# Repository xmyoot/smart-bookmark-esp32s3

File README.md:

# Smart Bookmark ESP32-S3 BLE

### Ultra-Low-Power Voice Recording & Audio Annotation Bookmark

---

## 3D Hardware Overview

---

## Project Highlights
The **Smart Bookmark** is a commercial-grade, ultra-thin 4-layer hardware device designed to fit cleanly inside a book or notebook. It records spoken voice memos, audio book notes, and timestamps via a single push-button, storing high-quality audio onto 16 MB onboard flash and syncing via Bluetooth Low Energy (BLE 5.0) to an accompanying mobile application.

### Key Features
- **Processor:** Espressif **ESP32-S3-WROOM-1** (Dual-core Xtensa LX7 @ 240 MHz, 2.4 GHz Wi-Fi & BLE 5.0).
- **Audio Capture:** Knowles digital PDM / MEMS microphone (`MK1`) with hardware audio filtering.
- **Local Storage:** 16 MB high-speed SPI NOR Flash (`U6`) dedicated for raw and compressed audio memo storage.
- **Power Management:**
  - Integrated single-cell LiPo charger (`U3`, TP4056/MCP73831 class) with USB-C power input (`J1`).
  - Ultra-low quiescent current 3.3V LDO regulator (`U5`).
  - Precision battery level monitoring voltage divider (`BATT SENSE` / `U4`).
- **Physical Design:**
  - 37.1 × 52.1 mm form factor with rounded corners to protect paper pages.
  - Symmetrical component placement with clear silkscreen identifiers (`STATUS LED`, `16MB FLASH`, `RECORD SW1`, `U3 CHARGER`, `3V3 REG`).
  - Dedicated bottom-side battery cradle target (`CELL 25 × 30 mm`) and 2×3 pogo-pin programming test matrix (`GND`, `3V3`, `EN`, `BOOT`, `TX`, `RX`).

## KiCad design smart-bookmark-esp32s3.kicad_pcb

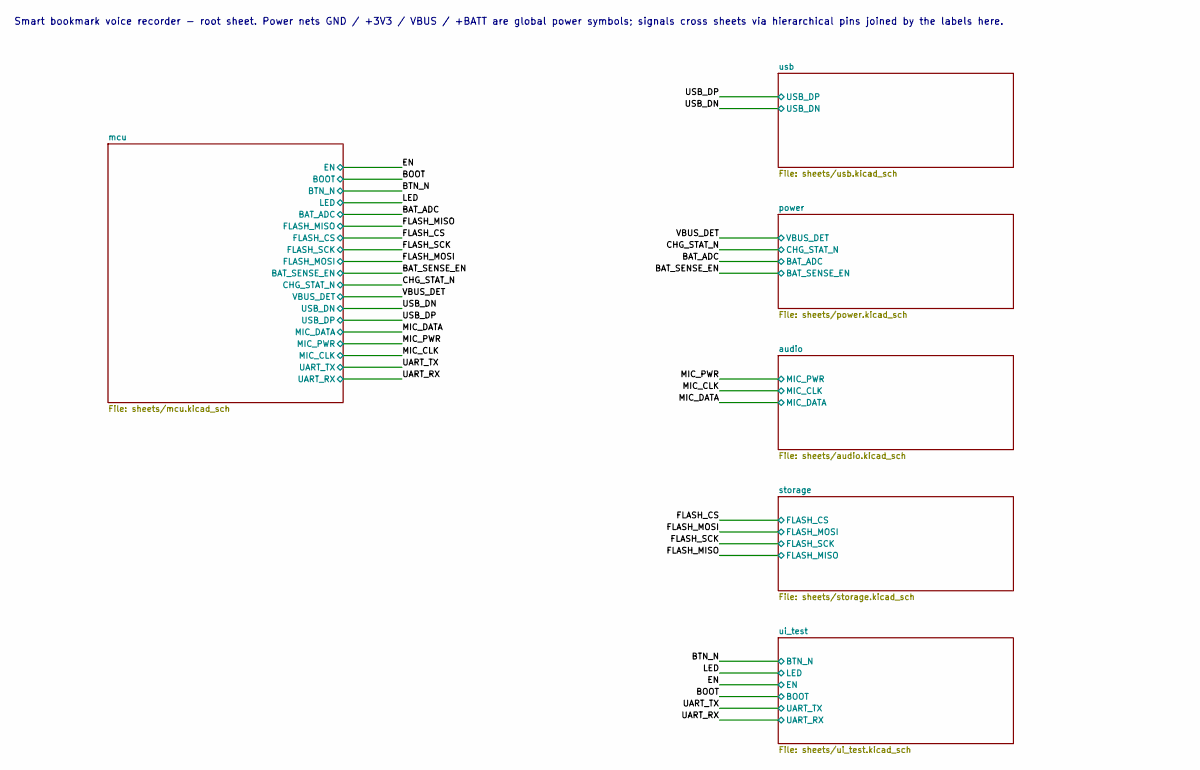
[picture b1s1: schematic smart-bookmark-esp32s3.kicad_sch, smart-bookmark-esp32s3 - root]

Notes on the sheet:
Smart bookmark voice recorder - root sheet. Power nets GND / +3V3 / VBUS / +BATT are global power symbols; signals cross sheets via hierarchical pins joined by the labels here.

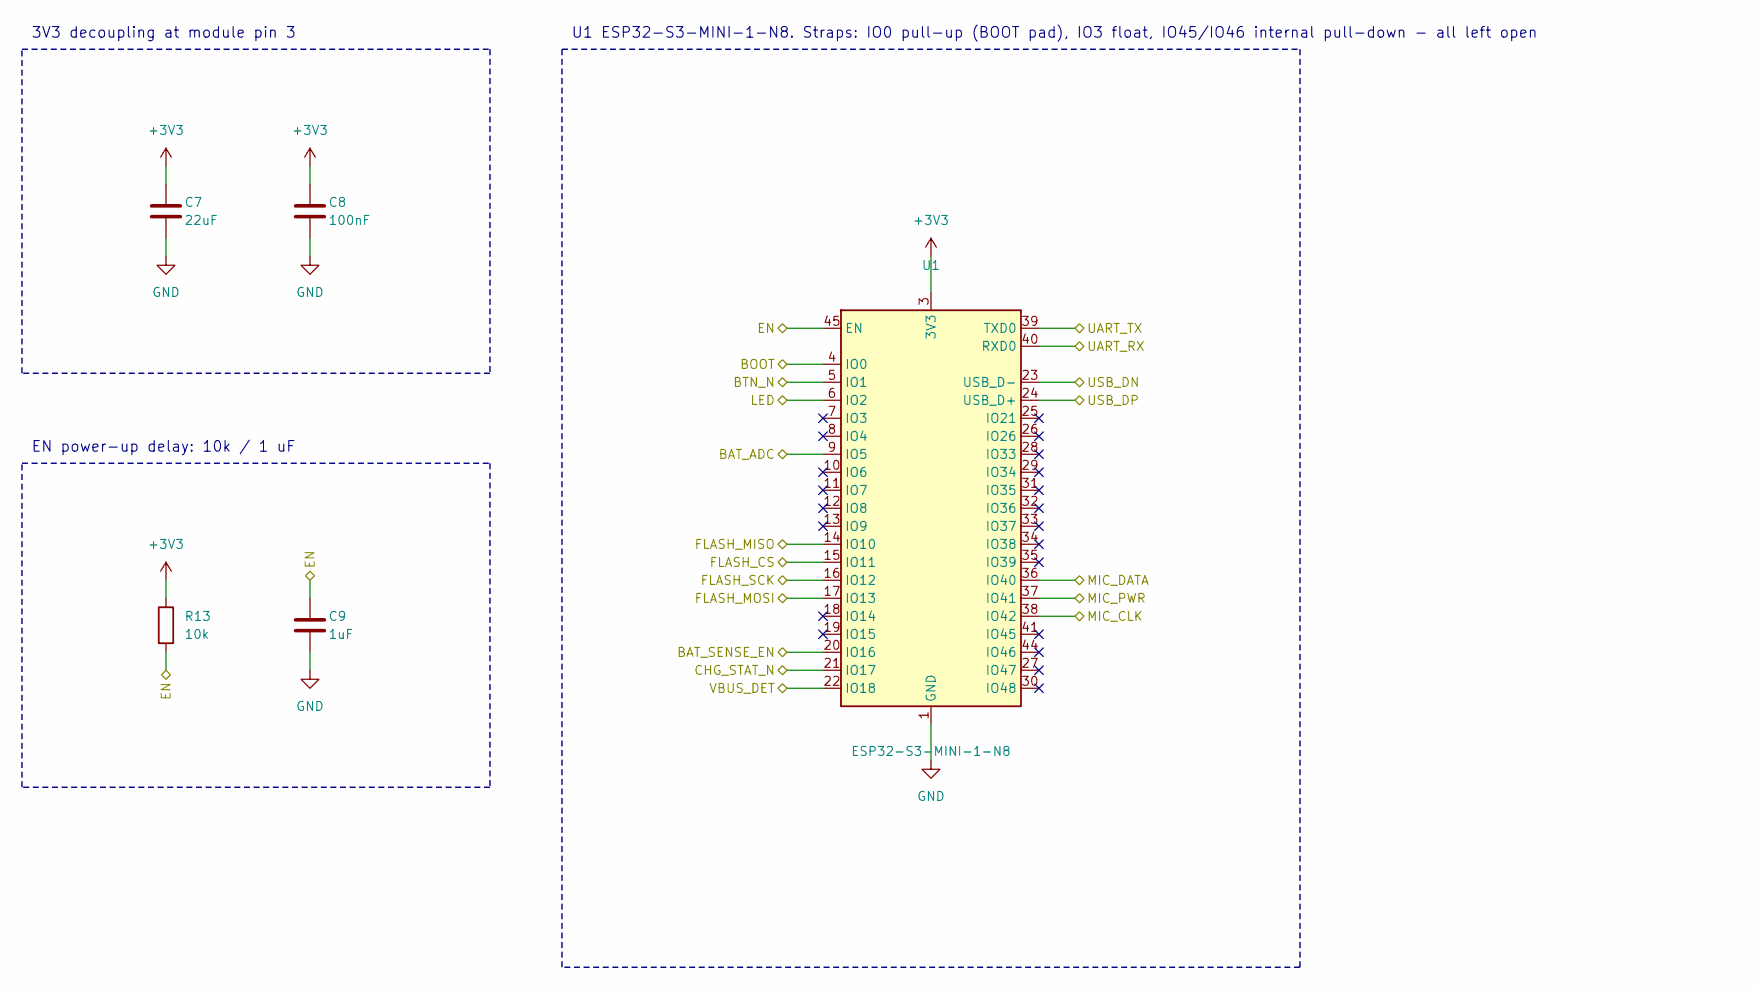
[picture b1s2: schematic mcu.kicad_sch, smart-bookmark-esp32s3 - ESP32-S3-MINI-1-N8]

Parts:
C7: 22uF; C_0805_2012Metric; MPN CL21A226MAQNNNE; LCSC C45783
C8: 100nF; C_0402_1005Metric; MPN CL05B104KO5NNNC; LCSC C1525
C9: 1uF; C_0402_1005Metric; MPN CL05A105KA5NQNC; LCSC C52923
R13: 10k; R_0402_1005Metric; MPN 0402WGF1002TCE; LCSC C25744
U1: ESP32-S3-MINI-1-N8; ESP32-S2-MINI-1; MPN ESP32-S3-MINI-1-N8; LCSC C2913206

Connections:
+3V3: C7.1, C8.1, R13.1, U1.3 (3V3); also elsewhere on the board
/BAT_ADC: U1.9 (IO5); also elsewhere on the board
/BAT_SENSE_EN: U1.20 (IO16); also elsewhere on the board
/BOOT: U1.4 (IO0); also elsewhere on the board
/BTN_N: U1.5 (IO1); also elsewhere on the board
/CHG_STAT_N: U1.21 (IO17); also elsewhere on the board
/EN: C9.1, R13.2, U1.45 (EN); also elsewhere on the board
/FLASH_CS: U1.15 (IO11); also elsewhere on the board
/FLASH_MISO: U1.14 (IO10); also elsewhere on the board
/FLASH_MOSI: U1.17 (IO13); also elsewhere on the board
/FLASH_SCK: U1.16 (IO12); also elsewhere on the board
/LED: U1.6 (IO2); also elsewhere on the board
/MIC_CLK: U1.38 (IO42); also elsewhere on the board
/MIC_DATA: U1.36 (IO40); also elsewhere on the board
/MIC_PWR: U1.37 (IO41); also elsewhere on the board
/UART_RX: U1.40 (RXD0); also elsewhere on the board
/UART_TX: U1.39 (TXD0); also elsewhere on the board
/USB_DN: U1.23 (USB_D-); also elsewhere on the board
/USB_DP: U1.24 (USB_D+); also elsewhere on the board
/VBUS_DET: U1.22 (IO18); also elsewhere on the board
GND: C7.2, C8.2, C9.2, U1.1 (GND), U1.2 (GND), U1.42 (GND), U1.43 (GND), U1.46 (GND), U1.47 (GND), U1.48 (GND), U1.49 (GND), U1.50 (GND), U1.51 (GND), U1.52 (GND), U1.53 (GND), U1.54 (GND), U1.55 (GND), U1.56 (GND), U1.57 (GND), U1.58 (GND), U1.59 (GND), U1.60 (GND), U1.61 (GND), U1.62 (GND), U1.63 (GND), U1.64 (GND), U1.65 (GND); also elsewhere on the board

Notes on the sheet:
U1 ESP32-S3-MINI-1-N8. Straps: IO0 pull-up (BOOT pad), IO3 float, IO45/IO46 internal pull-down - all left open
3V3 decoupling at module pin 3
EN power-up delay: 10k / 1 uF

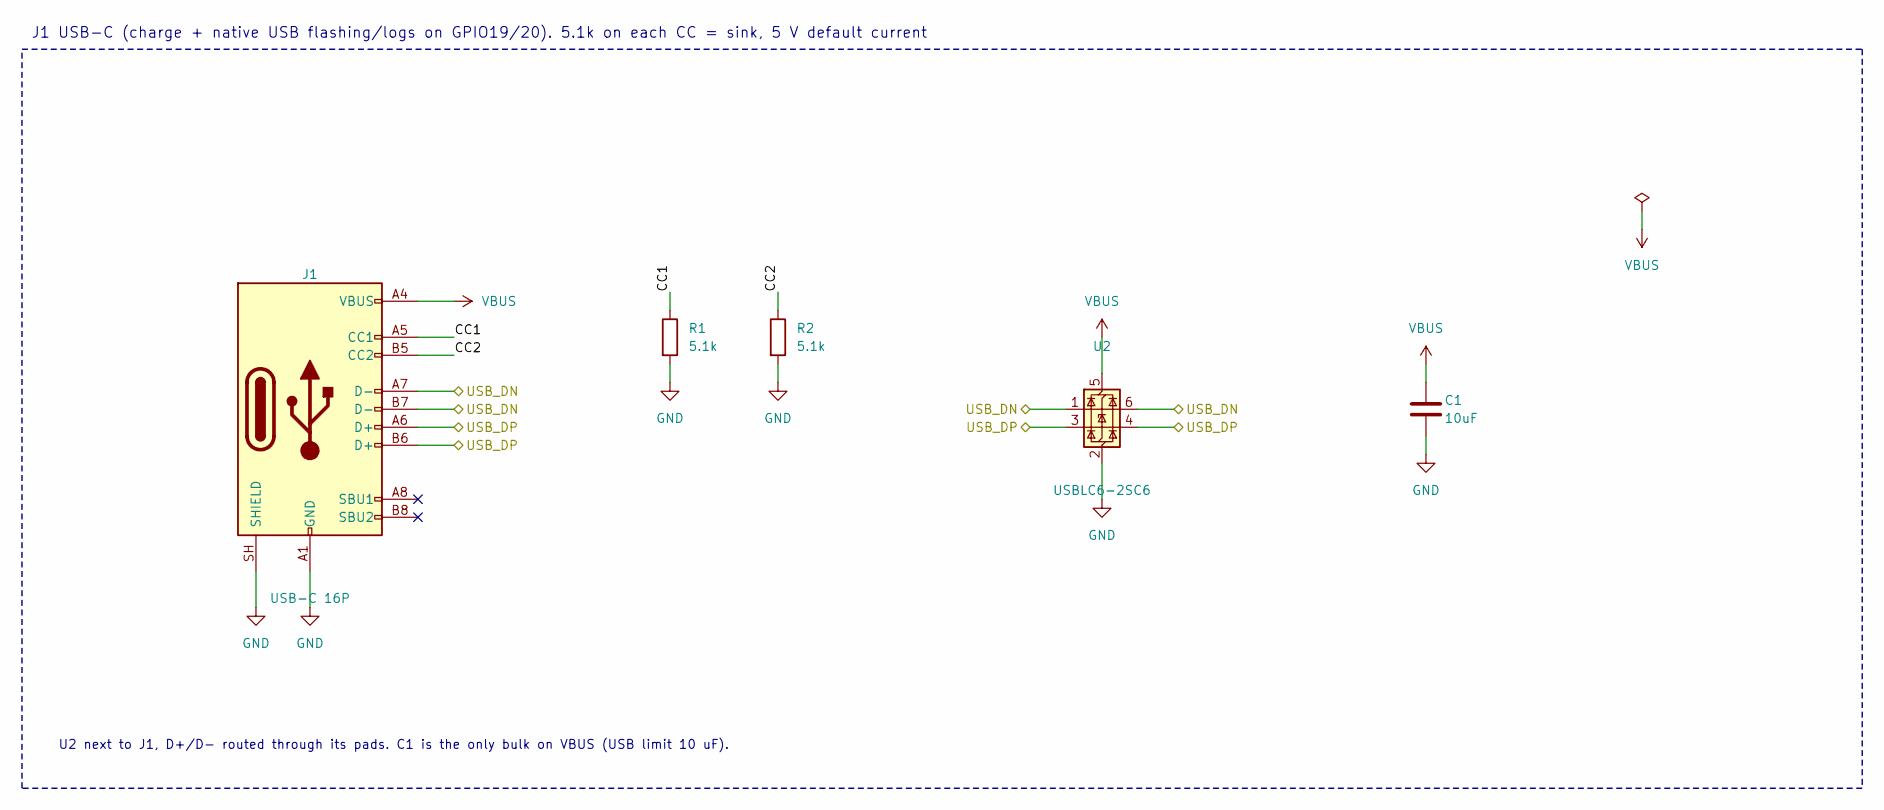
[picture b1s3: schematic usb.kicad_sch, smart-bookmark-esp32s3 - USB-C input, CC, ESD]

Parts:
C1: 10uF; C_0603_1608Metric; MPN CL10A106KP8NNNC; LCSC C19702
J1: USB-C 16P; USB_C_Receptacle_HRO_TYPE-C-31-M-12; MPN TYPE-C-31-M-12; LCSC C165948
R1, R2: 5.1k; R_0402_1005Metric; MPN 0402WGF5101TCE; LCSC C25905
U2: USBLC6-2SC6; SOT-23-6; MPN USBLC6-2SC6; LCSC C7519

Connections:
/USB_DN: J1.A7 (D-), J1.B7 (D-), U2.1 (I/O1), U2.6 (I/O1); also elsewhere on the board
/USB_DP: J1.A6 (D+), J1.B6 (D+), U2.3 (I/O2), U2.4 (I/O2); also elsewhere on the board
/usb/CC1: J1.A5 (CC1), R1.1
/usb/CC2: J1.B5 (CC2), R2.1
GND: C1.2, J1.A1 (GND), J1.A12 (GND), J1.B1 (GND), J1.B12 (GND), J1.SH (SHIELD), R1.2, R2.2, U2.2 (GND); also elsewhere on the board
VBUS: C1.1, J1.A4 (VBUS), J1.A9 (VBUS), J1.B4 (VBUS), J1.B9 (VBUS), U2.5 (VBUS); also elsewhere on the board

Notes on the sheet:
J1 USB-C (charge + native USB flashing/logs on GPIO19/20). 5.1k on each CC = sink, 5 V default current
U2 next to J1, D+/D- routed through its pads. C1 is the only bulk on VBUS (USB limit 10 uF).

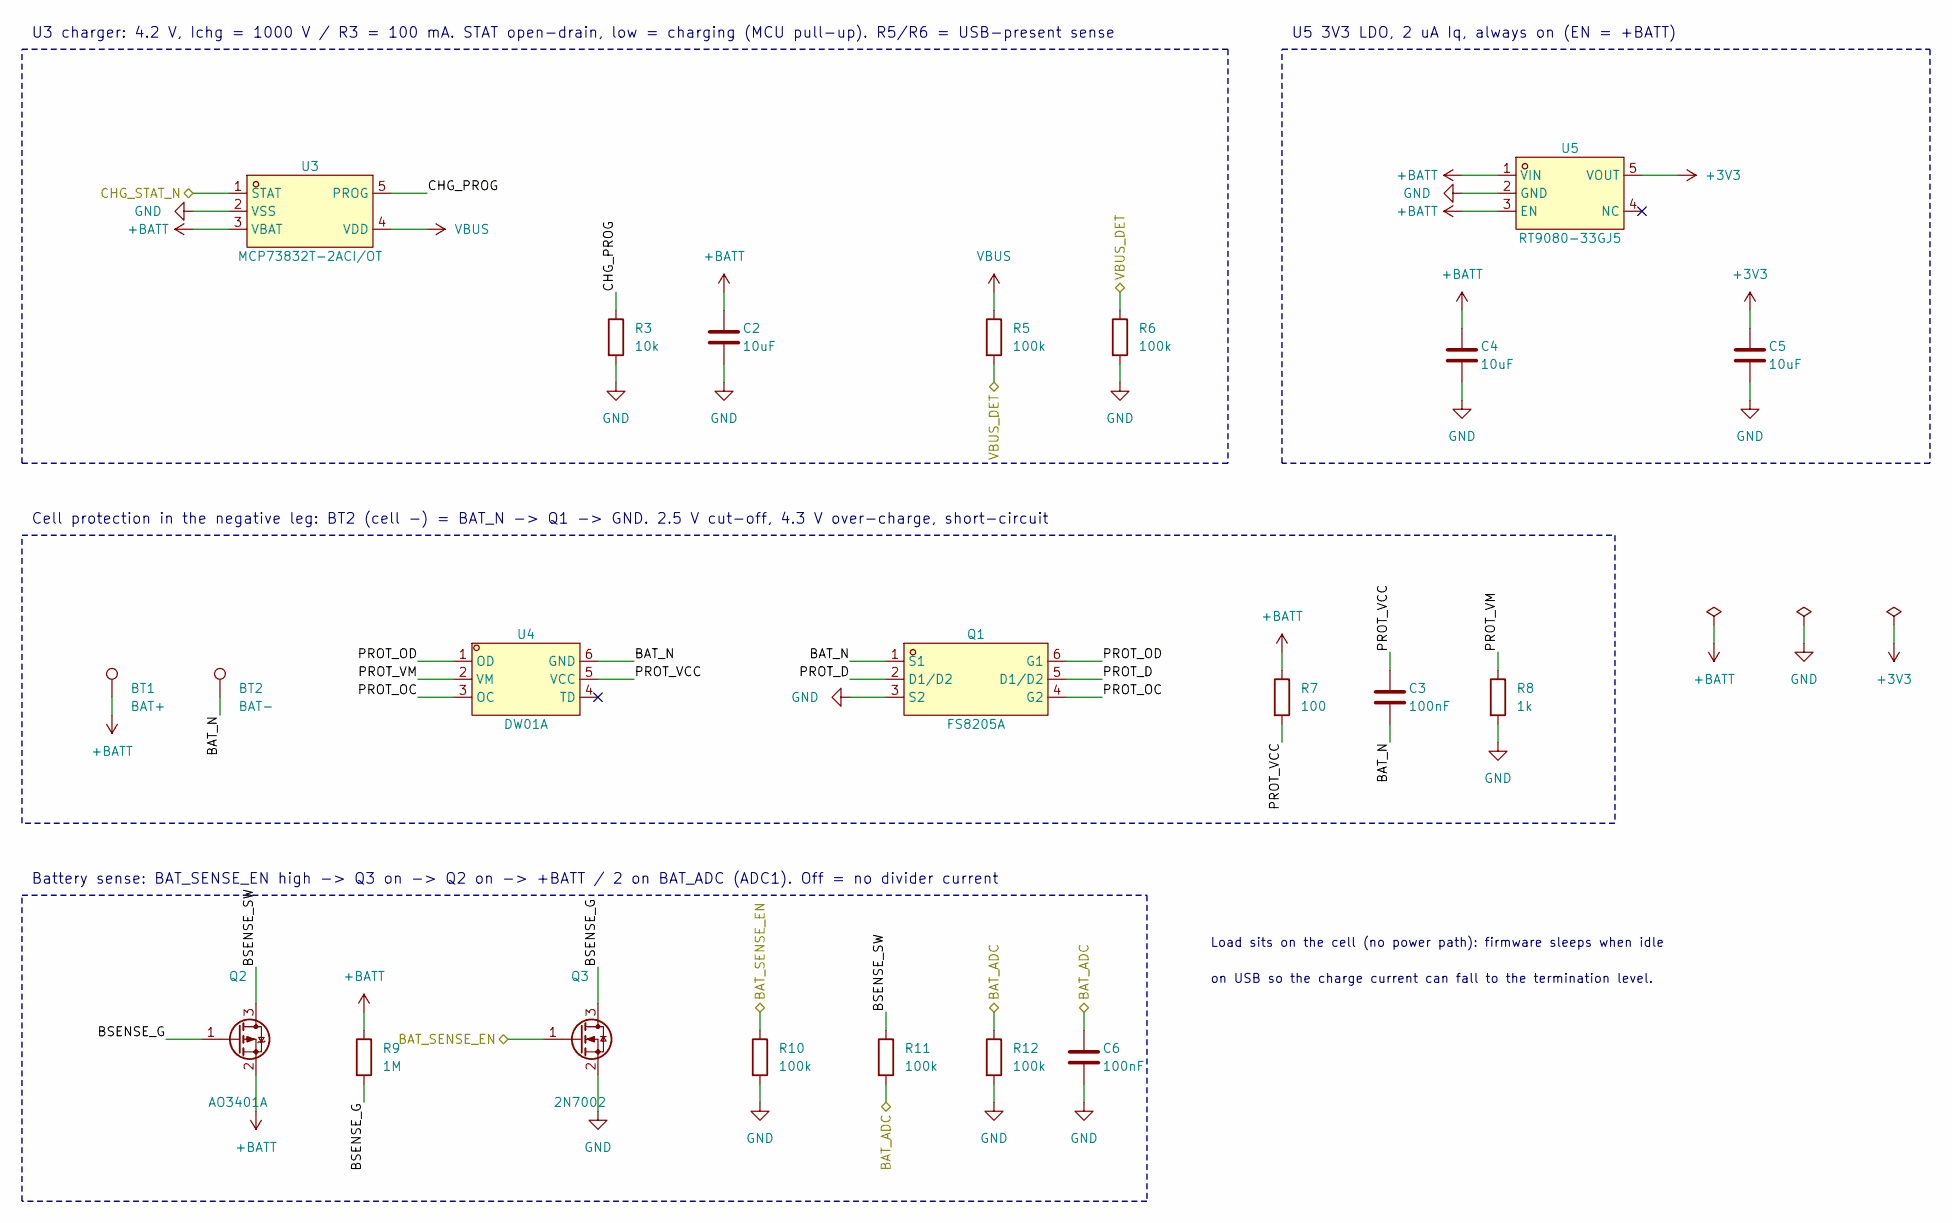
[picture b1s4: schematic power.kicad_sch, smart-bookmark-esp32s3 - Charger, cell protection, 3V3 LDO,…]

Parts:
BT1: BAT+; TestPoint_Pad_2.5x2.5mm
BT2: BAT-; TestPoint_Pad_2.5x2.5mm
C2, C4, C5: 10uF; C_0603_1608Metric; MPN CL10A106KP8NNNC; LCSC C19702
C3, C6: 100nF; C_0402_1005Metric; MPN CL05B104KO5NNNC; LCSC C1525
Q1: FS8205A; SOT-23-6; MPN FS8205A; LCSC C908265
Q2: AO3401A; SOT-23; MPN AO3401A; LCSC C15127
Q3: 2N7002; SOT-23; MPN 2N7002; LCSC C8545
R3: 10k; R_0402_1005Metric; MPN 0402WGF1002TCE; LCSC C25744
R5, R6, R10, R11, R12: 100k; R_0402_1005Metric; MPN 0402WGF1003TCE; LCSC C25741
R7: 100; R_0402_1005Metric; MPN 0402WGF1000TCE; LCSC C25076
R8: 1k; R_0402_1005Metric; MPN 0402WGF1001TCE; LCSC C11702
R9: 1M; R_0402_1005Metric; MPN 0402WGF1004TCE; LCSC C26083
U3: MCP73832T-2ACI/OT; SOT-23-5; MPN MCP73832T-2ACI/OT; LCSC C38066
U4: DW01A; SOT-23-6; MPN DW01A; LCSC C351410
U5: RT9080-33GJ5; TSOT-23-5; MPN RT9080-33GJ5; LCSC C841192

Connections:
+3V3: C5.1, U5.5 (VOUT); also elsewhere on the board
+BATT: BT1.1, C2.1, C4.1, Q2.2 (S), R7.1, R9.1, U3.3 (VBAT), U5.1 (VIN), U5.3 (EN); also elsewhere on the board
/BAT_ADC: C6.1, R11.2, R12.1; also elsewhere on the board
/BAT_SENSE_EN: Q3.1 (G), R10.1; also elsewhere on the board
/CHG_STAT_N: U3.1 (STAT); also elsewhere on the board
/VBUS_DET: R5.2, R6.1; also elsewhere on the board
/power/BAT_N: BT2.1, C3.2, Q1.1 (S1), U4.6 (GND)
/power/BSENSE_G: Q2.1 (G), Q3.3 (D), R9.2
/power/BSENSE_SW: Q2.3 (D), R11.1
/power/CHG_PROG: R3.1, U3.5 (PROG)
/power/PROT_D: Q1.2 (D1/D2), Q1.5 (D1/D2)
/power/PROT_OC: Q1.4 (G2), U4.3 (OC)
/power/PROT_OD: Q1.6 (G1), U4.1 (OD)
/power/PROT_VCC: C3.1, R7.2, U4.5 (VCC)
/power/PROT_VM: R8.1, U4.2 (VM)
GND: C2.2, C4.2, C5.2, C6.2, Q1.3 (S2), Q3.2 (S), R3.2, R6.2, R8.2, R10.2, R12.2, U3.2 (VSS), U5.2 (GND); also elsewhere on the board
VBUS: R5.1, U3.4 (VDD); also elsewhere on the board

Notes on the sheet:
U3 charger: 4.2 V, Ichg = 1000 V / R3 = 100 mA. STAT open-drain, low = charging (MCU pull-up). R5/R6 = USB-present sense
U5 3V3 LDO, 2 uA Iq, always on (EN = +BATT)
Cell protection in the negative leg: BT2 (cell -) = BAT_N -> Q1 -> GND. 2.5 V cut-off, 4.3 V over-charge, short-circuit
Battery sense: BAT_SENSE_EN high -> Q3 on -> Q2 on -> +BATT / 2 on BAT_ADC (ADC1). Off = no divider current
Load sits on the cell (no power path): firmware sleeps when idle
on USB so the charge current can fall to the termination level.

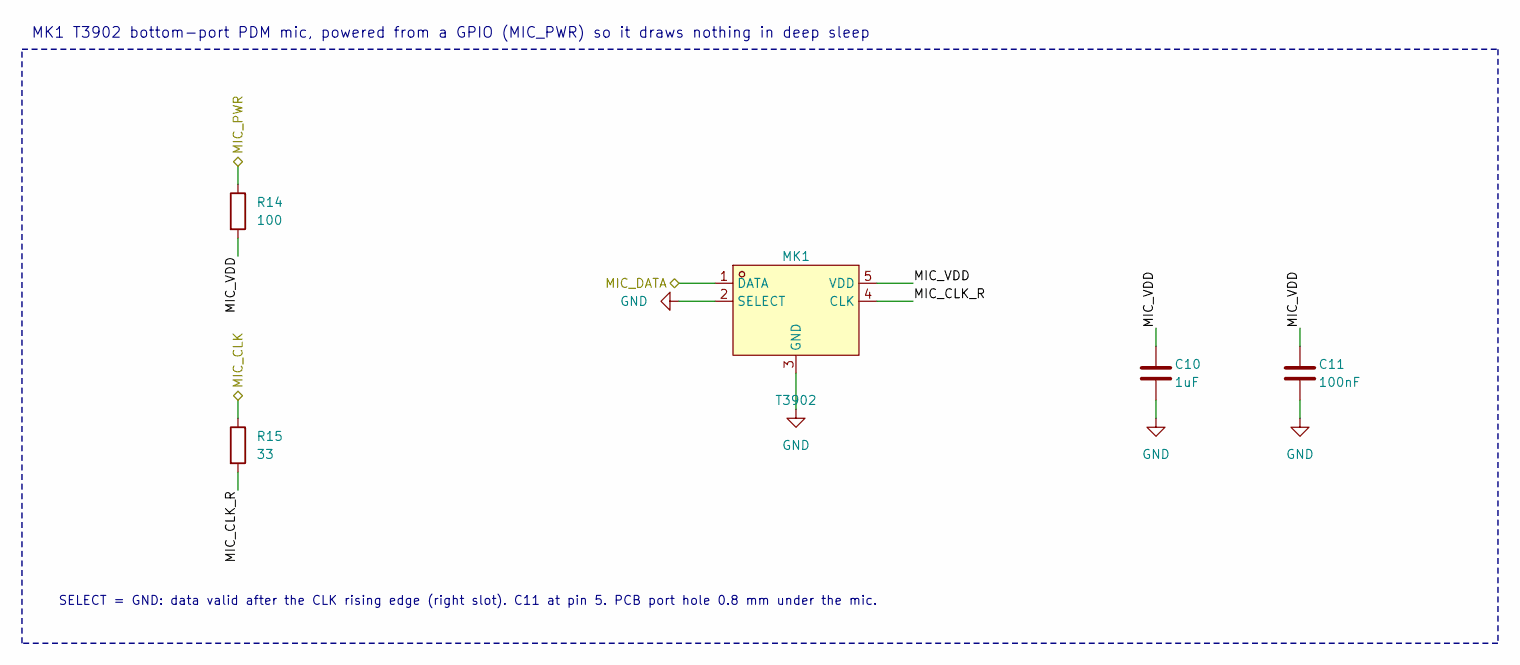
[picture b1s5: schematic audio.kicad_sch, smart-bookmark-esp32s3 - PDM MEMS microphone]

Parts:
C10: 1uF; C_0402_1005Metric; MPN CL05A105KA5NQNC; LCSC C52923
C11: 100nF; C_0402_1005Metric; MPN CL05B104KO5NNNC; LCSC C1525
MK1: T3902; MIC-SMD_5P-L3.5-W2.7-TL_MMICT390200012; MPN MMICT390200012; LCSC C3171752
R14: 100; R_0402_1005Metric; MPN 0402WGF1000TCE; LCSC C25076
R15: 33; R_0402_1005Metric; MPN 0402WGF330JTCE; LCSC C25105

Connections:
/MIC_CLK: R15.1; also elsewhere on the board
/MIC_DATA: MK1.1 (DATA); also elsewhere on the board
/MIC_PWR: R14.1; also elsewhere on the board
/audio/MIC_CLK_R: MK1.4 (CLK), R15.2
/audio/MIC_VDD: C10.1, C11.1, MK1.5 (VDD), R14.2
GND: C10.2, C11.2, MK1.2 (SELECT), MK1.3 (GND); also elsewhere on the board

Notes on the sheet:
MK1 T3902 bottom-port PDM mic, powered from a GPIO (MIC_PWR) so it draws nothing in deep sleep
SELECT = GND: data valid after the CLK rising edge (right slot). C11 at pin 5. PCB port hole 0.8 mm under the mic.

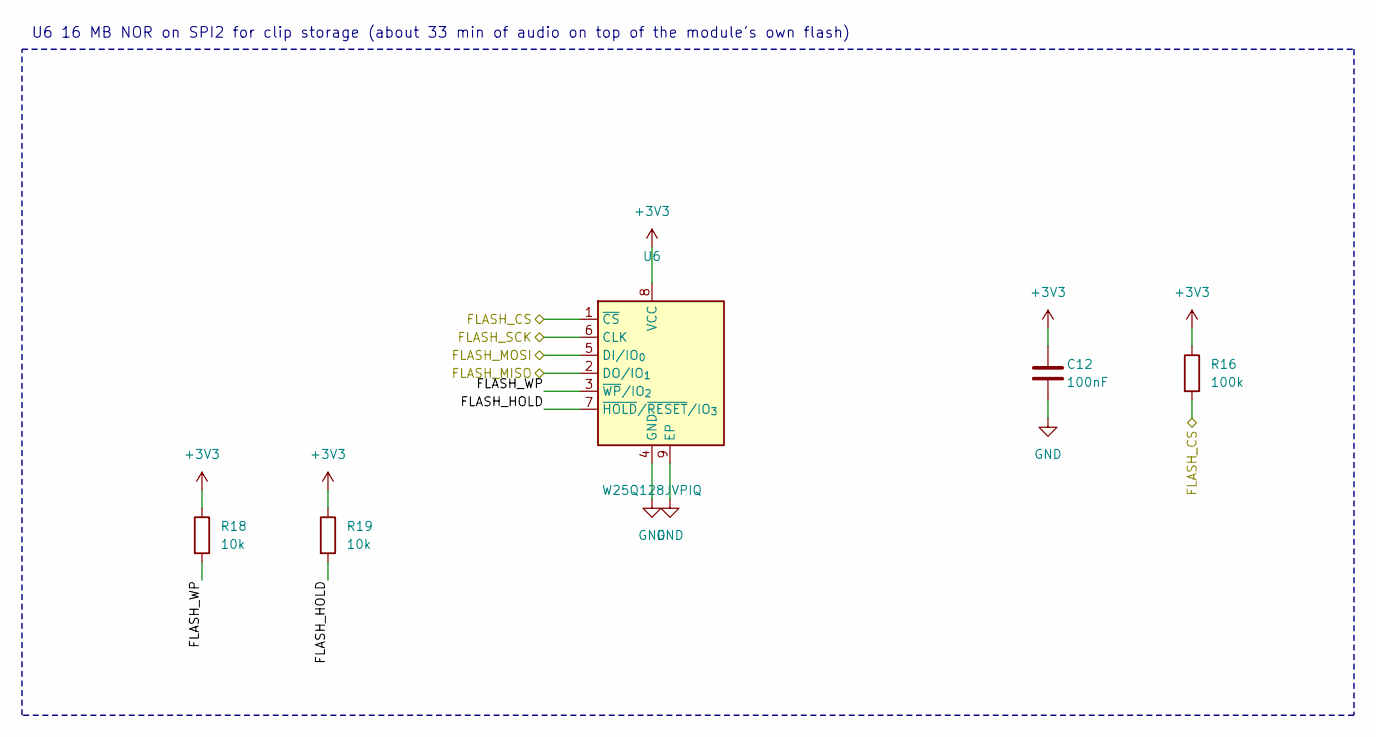
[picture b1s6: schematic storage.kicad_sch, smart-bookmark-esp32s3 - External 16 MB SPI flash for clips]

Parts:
C12: 100nF; C_0402_1005Metric; MPN CL05B104KO5NNNC; LCSC C1525
R16: 100k; R_0402_1005Metric; MPN 0402WGF1003TCE; LCSC C25741
R18, R19: 10k; R_0402_1005Metric; MPN 0402WGF1002TCE; LCSC C25744
U6: W25Q128JVPIQ; WSON-8-1EP_6x5mm_P1.27mm_EP3.4x4.3mm; MPN W25Q128JVPIQ; LCSC C190862

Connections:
+3V3: C12.1, R16.1, R18.1, R19.1, U6.8 (VCC); also elsewhere on the board
/FLASH_CS: R16.2, U6.1 (~CS); also elsewhere on the board
/FLASH_MISO: U6.2 (DO/IO_{1}); also elsewhere on the board
/FLASH_MOSI: U6.5 (DI/IO_{0}); also elsewhere on the board
/FLASH_SCK: U6.6 (CLK); also elsewhere on the board
/storage/FLASH_HOLD: R19.2, U6.7 (~HOLD/~RESET/IO_{3})
/storage/FLASH_WP: R18.2, U6.3 (~WP/IO_{2})
GND: C12.2, U6.4 (GND), U6.9 (EP); also elsewhere on the board

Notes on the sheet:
U6 16 MB NOR on SPI2 for clip storage (about 33 min of audio on top of the module's own flash)

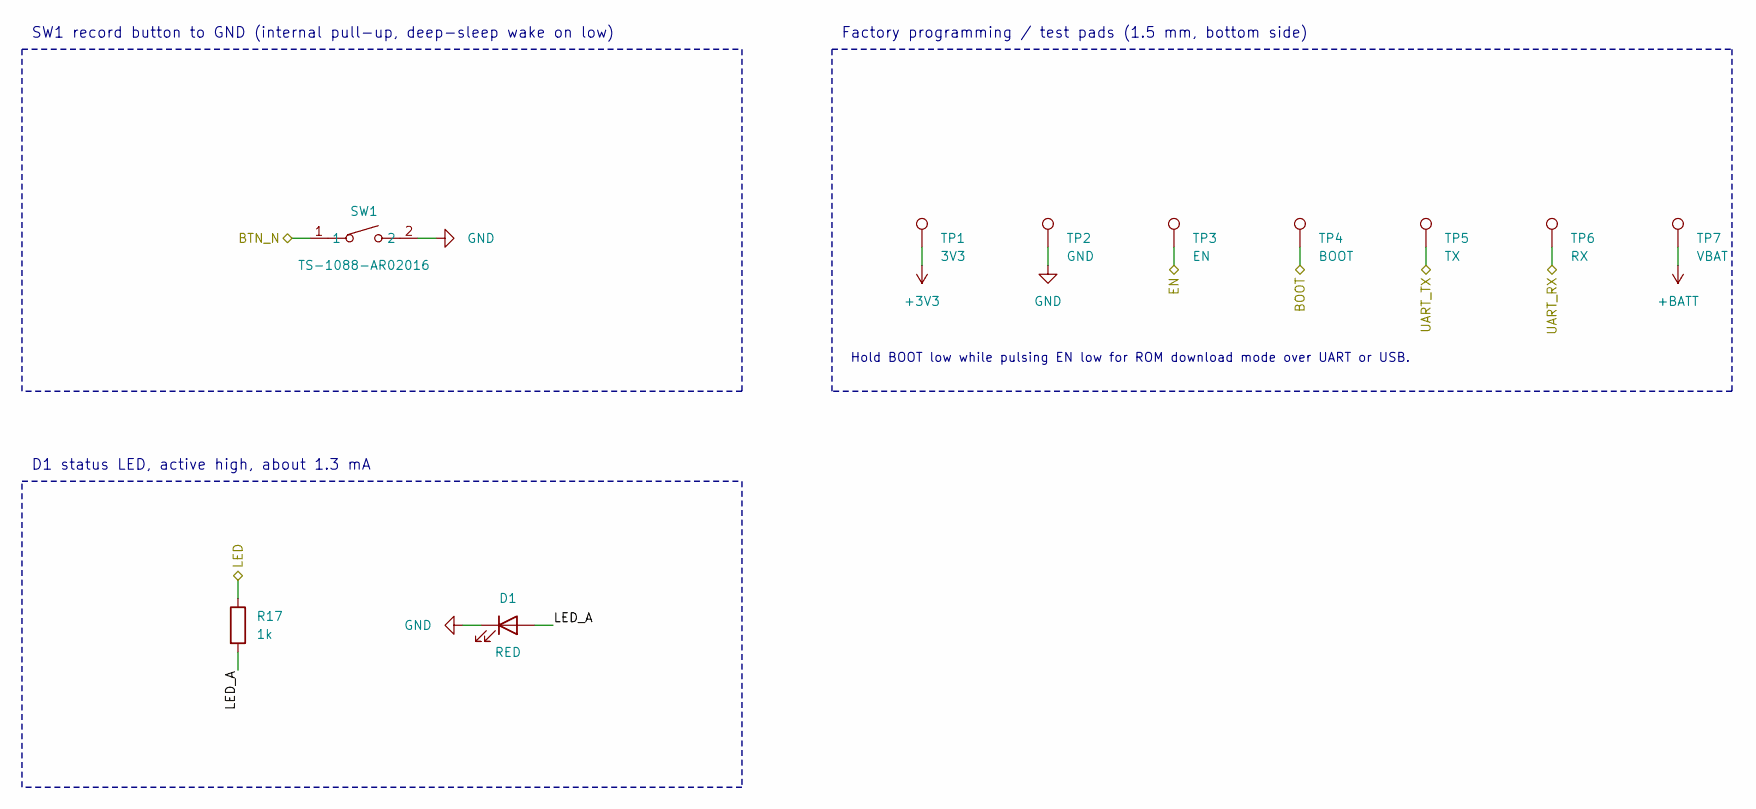
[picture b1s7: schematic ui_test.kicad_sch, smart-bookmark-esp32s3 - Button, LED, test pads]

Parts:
D1: RED; LED_0603_1608Metric; MPN KT-0603R; LCSC C2286
R17: 1k; R_0402_1005Metric; MPN 0402WGF1001TCE; LCSC C11702
SW1: TS-1088-AR02016; SW-SMD_L3.9-W3.0-P4.45; MPN TS-1088-AR02016; LCSC C720477
TP1: 3V3; TestPoint_Pad_D1.5mm
TP2: GND; TestPoint_Pad_D1.5mm
TP3: EN; TestPoint_Pad_D1.5mm
TP4: BOOT; TestPoint_Pad_D1.5mm
TP5: TX; TestPoint_Pad_D1.5mm
TP6: RX; TestPoint_Pad_D1.5mm
TP7: VBAT; TestPoint_Pad_D1.5mm

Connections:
+3V3: TP1.1; also elsewhere on the board
+BATT: TP7.1; also elsewhere on the board
/BOOT: TP4.1; also elsewhere on the board
/BTN_N: SW1.1; also elsewhere on the board
/EN: TP3.1; also elsewhere on the board
/LED: R17.1; also elsewhere on the board
/UART_RX: TP6.1; also elsewhere on the board
/UART_TX: TP5.1; also elsewhere on the board
/ui_test/LED_A: D1.2 (A), R17.2
GND: D1.1 (K), SW1.2, TP2.1; also elsewhere on the board

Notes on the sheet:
SW1 record button to GND (internal pull-up, deep-sleep wake on low)
D1 status LED, active high, about 1.3 mA
Factory programming / test pads (1.5 mm, bottom side)
Hold BOOT low while pulsing EN low for ROM download mode over UART or USB.

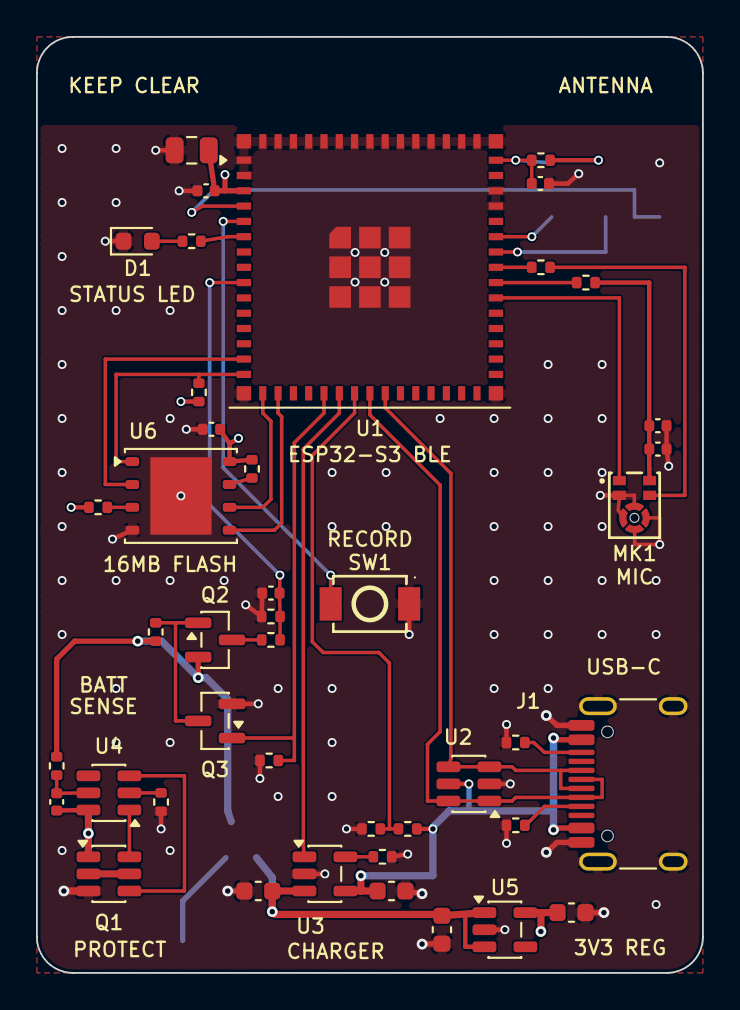
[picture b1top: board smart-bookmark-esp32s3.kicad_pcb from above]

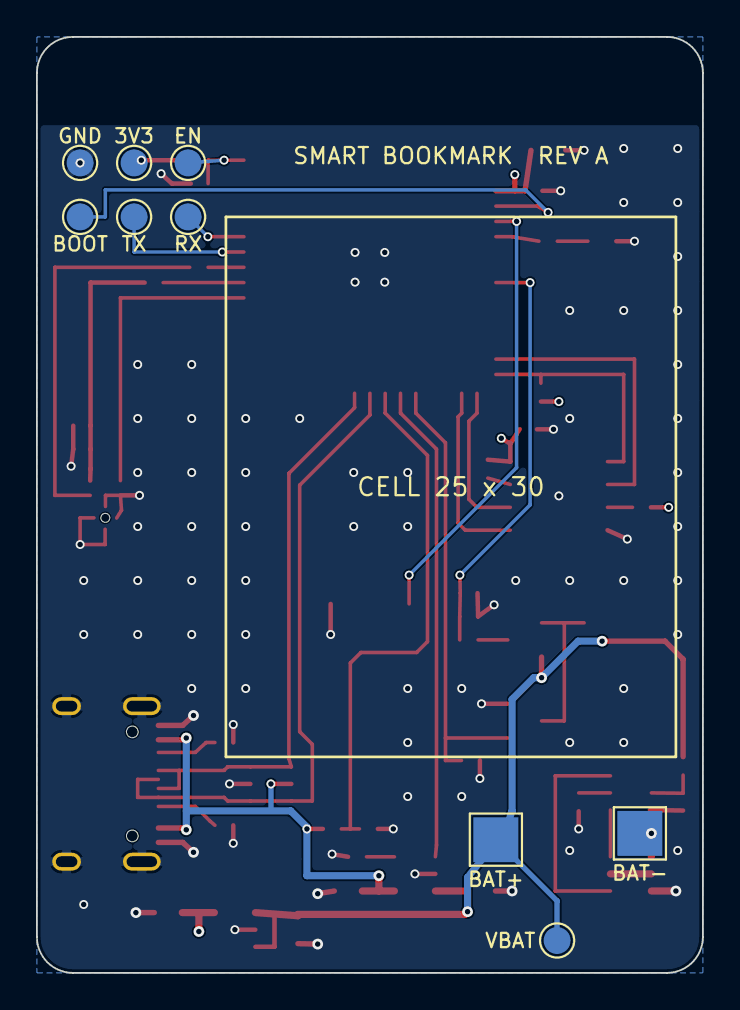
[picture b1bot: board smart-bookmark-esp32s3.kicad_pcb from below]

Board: 4 copper layers, 37.0 x 52.0 mm, 52 parts (9 on the bottom side), 39 nets.

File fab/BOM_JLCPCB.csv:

Comment,Designator,Footprint,LCSC Part #
10uF CL10A106KP8NNNC,"C1,C2,C4,C5",C_0603_1608Metric,C19702
100nF CL05B104KO5NNNC,"C3,C6,C8,C11,C12",C_0402_1005Metric,C1525
22uF CL21A226MAQNNNE,C7,C_0805_2012Metric,C45783
1uF CL05A105KA5NQNC,"C9,C10",C_0402_1005Metric,C52923
RED KT-0603R,D1,LED_0603_1608Metric,C2286
USB-C 16P TYPE-C-31-M-12,J1,USB_C_Receptacle_HRO_TYPE-C-31-M-12,C165948
T3902 MMICT390200012,MK1,MIC-SMD_5P-L3.5-W2.7-TL_MMICT390200012,C3171752
FS8205A,Q1,SOT-23-6,C908265
AO3401A,Q2,SOT-23,C15127
2N7002,Q3,SOT-23,C8545
5.1k 0402WGF5101TCE,"R1,R2",R_0402_1005Metric,C25905
10k 0402WGF1002TCE,"R3,R13,R18,R19",R_0402_1005Metric,C25744
100k 0402WGF1003TCE,"R5,R6,R10,R11,R12,R16",R_0402_1005Metric,C25741
100 0402WGF1000TCE,"R7,R14",R_0402_1005Metric,C25076
1k 0402WGF1001TCE,"R8,R17",R_0402_1005Metric,C11702
1M 0402WGF1004TCE,R9,R_0402_1005Metric,C26083
33 0402WGF330JTCE,R15,R_0402_1005Metric,C25105
TS-1088-AR02016,SW1,SW-SMD_L3.9-W3.0-P4.45,C720477
ESP32-S3-MINI-1-N8,U1,ESP32-S2-MINI-1,C2913206
USBLC6-2SC6,U2,SOT-23-6,C7519
MCP73832T-2ACI/OT,U3,SOT-23-5,C38066
DW01A,U4,SOT-23-6,C351410
RT9080-33GJ5,U5,TSOT-23-5,C841192
W25Q128JVPIQ,U6,WSON-8-1EP_6x5mm_P1.27mm_EP3.4x4.3mm,C190862

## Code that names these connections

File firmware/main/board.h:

/* Pin map and product constants for the smart bookmark board, Rev A.
 * Mirrors docs/design_spec.md section 3. Change a pin here and nowhere else. */
#pragma once

#include "driver/gpio.h"

/* ---- pins ---------------------------------------------------------------- */
#define PIN_BUTTON        GPIO_NUM_1    /* SW1 to GND, internal pull-up, RTC wake on low */
#define PIN_LED           GPIO_NUM_2    /* D1, active high */
#define PIN_BAT_ADC       GPIO_NUM_5    /* ADC1_CH4: +BATT / 2 while PIN_BAT_SENSE_EN is high */
#define BAT_ADC_CHANNEL   ADC_CHANNEL_4
#define PIN_BAT_SENSE_EN  GPIO_NUM_16   /* high = battery divider connected */
#define PIN_CHG_STAT_N    GPIO_NUM_17   /* open drain from the charger: low = charging */
#define PIN_VBUS_DET      GPIO_NUM_18   /* VBUS / 2: high = USB present, RTC wake on high */
#define PIN_MIC_DATA      GPIO_NUM_40
#define PIN_MIC_PWR       GPIO_NUM_41   /* powers the microphone; low = off */
#define PIN_MIC_CLK       GPIO_NUM_42

/* External 16 MB clip flash U6 on SPI2 */
#define PIN_FLASH_MISO    GPIO_NUM_10
#define PIN_FLASH_CS      GPIO_NUM_11
#define PIN_FLASH_SCK     GPIO_NUM_12
#define PIN_FLASH_MOSI    GPIO_NUM_13

/* ---- audio ---------------------------------------------------------------- */
#define AUDIO_SAMPLE_RATE     16000
#define AUDIO_GAIN_SHIFT      2         /* PCM is multiplied by 2^n before encoding, with saturation */
#define AUDIO_MIC_SETTLE_MS   120       /* discarded after mic power-up (T3902 wake-up + filter settle) */
#define AUDIO_MIC_SLOT_RIGHT  1         /* T3902 SELECT pin is tied to GND = "right" PDM slot */
#define CLIP_MAX_SECONDS      120
#define CLIP_MIN_MS           400       /* shorter presses are treated as "wake up and sync" */

/* ---- battery -------------------------------------------------------------- */
#define BAT_DIVIDER           2         /* R11 = R12 */
#define BAT_EMPTY_MV          3300      /* refuse to record below this */
#define BAT_FULL_MV           4150

/* ---- behaviour ------------------------------------------------------------ */
#define ADV_AFTER_CLIP_S      30        /* advertise this long after a recording or a button tap */
#define ADV_ON_USB_S          60
#define IDLE_CONNECTED_S      20        /* drop to sleep after this long connected with no traffic */
#define BLE_REQUIRE_ENCRYPTION 1        /* 1 = clip data needs a bonded, encrypted link */
#define DEVICE_NAME           "Bookmark"
#define FW_VERSION_MAJOR      0
#define FW_VERSION_MINOR      1
